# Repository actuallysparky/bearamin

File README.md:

# Bearamin

A whole copse of Bearamin friends. I made this family of optical instruments to turn a little motion into a lot of musical possibility.

Move your paw above an 8×8 depth sensor to shape X, Y and Z, find a note, open a gate, or give it a Spank. Pick the Bearamin that fits your patch:

| Bearamin | What it does | What you need |
| --- | --- | --- |
| [Bearamin Lite](bearamin-lite/README.md) | Gesture-controlled Eurorack CV and gates, plus USB and Bluetooth MIDI | Optical VL53L7CX sensor  paired with an ESP32-S3 Matrix |
| [Bearamin Virtual](bearamin-virtual/README.md) | Gesture control for VCV Rack and USB MIDI for your DAW | VL53L7CX sensor and an RP2040-Zero carrier |
| [Bearamin](bearamin/README.md) | A specialist nerd tool for droners: five sound and CV modes, presets, and a browser interface | Sensor head, MatrixCore, Wi-Fi sidecar, and a dsp.coffee DPT |

## Find your sound

The shared **[Bearamin Field Guide](https://actuallysparky.github.io/bearamin/)** hangs out in a cave by Salmon Lake and connects to Bearamin Lite and Bearamin Virtual, helping you map motion to MIDI, get the latest firmware for your device, and generally be cool af. USB MIDI works with Lite and Virtual; Bluetooth MIDI works with Lite. Use a browser that supports Web MIDI, such as Chrome or Edge.

## See Bearamin in action

**[Watch “Bearamin Jazz” (2:29)](bearamin/media/bearamin-jazz.mp4?raw=1)**

## Make a Bearamin

Want one but don't wanna singe your fur with a soldering iron? Stay tuned - built modules available soon from Hive Mind Synthesis. 

Each product folder contains its firmware source and current editable KiCad hardware designs. Virtual also includes its VCV Rack 2 plugin. The releases are **beta releases**; start with the instructions for your hardware and the matching firmware.

Build reports, patches, and musical experiments are welcome. [Open an issue](https://github.com/actuallysparky/bearamin/issues) and tell me what you’re making.

## A deep bow to Mutable Instruments

Bearamin’s resonator modes build on **Émilie Gillet’s extraordinary work at Mutable Instruments**. Rings and stmlib come from [pichenettes/eurorack](https://github.com/pichenettes/eurorack); their original copyright and MIT license notices are retained. Bearamin is an independent derivative project, with enormous gratitude for the generosity and imagination behind that work.

## Full credit to dsp.coffee

The full instrument is built on the **dsp.coffee DPT**, designed and openly shared by **Joe Misra**. It provides the Daisy-based audio engine, CV and gate I/O, and the expansion connection Bearamin uses. Explore the [DPT source](https://github.com/joemisra/dpt) and [dsp.coffee](https://dsp.coffee/).

## Other upstream work

This family also builds on the [Electro-Smith Daisy ecosystem](https://github.com/electro-smith/libDaisy), [Espressif Arduino core](https://github.com/espressif/arduino-esp32), [Raspberry Pi Pico SDK](https://github.com/raspberrypi/pico-sdk), [TinyUSB](https://github.com/hathach/tinyusb), [NimBLE-Arduino](https://github.com/h2zero/NimBLE-Arduino), [ArduinoJson](https://github.com/bblanchon/ArduinoJson), ST’s VL53L7CX sensor driver, and Adafruit’s [VL53L7CX](https://github.com/adafruit/Adafruit_VL53L7CX) and [NeoPixel](https://github.com/adafruit/Adafruit_NeoPixel) libraries. Virtual’s predecessor is [BearaminVirtual](https://github.com/actuallysparky/BearaminVirtual).

## License

The existing Bearamin source and hardware use the [MIT License](LICENSE). Third-party files retain their upstream licenses and notices. Virtual’s Rack plugin is licensed under GPL-3.0-or-later; its bundled Bearfield processor retains the MIT License.

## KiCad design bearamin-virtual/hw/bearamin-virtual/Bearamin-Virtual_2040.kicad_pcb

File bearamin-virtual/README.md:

# Bearamin Virtual

An optical gesture controller for VCV Rack and USB MIDI. The display lives in Rack; the hardware stays small.

A Waveshare RP2040-Zero connects to a VL53L7CX 8×8 depth sensor through the six-pin carrier. It presents USB serial and class-compliant USB MIDI at the same time, so Rack and your DAW can share the controller without a bridge process.

## Play

In VCV Rack 2, add **Bearamin Virtual**, then select its serial port in the module context menu. The module shows the depth field and provides X/Y/Z unipolar and bipolar CV, Presence and Spank outputs.

In your DAW, choose **Bearamin Virtual** as a MIDI input. Defaults: channel 1, CC 20/21/22 for X/Y/Z, CC 23 for Presence, and note 60 for Spank. Virtual uses USB; it has no Bluetooth or Wi-Fi.

Open the [Bearamin Field Guide](https://actuallysparky.github.io/bearamin/) to change MIDI and gesture settings or install the current firmware. After the initial UF2 installation, compatible application updates transfer through MIDI and preserve saved settings. The full UF2 includes the recovery loader; firmware before the new loader requires that initial installation.

## Sources

- `firmware/BearaminVirtual2040/`: Pico SDK firmware, sensor driver and recovery loader.
- `vcv/BearaminVirtual/`: Rack 2 plugin and panel assets.
- `hw/bearamin-virtual/`: current RP2040-Zero carrier, schematic and footprints.

These are beta releases. Sensor wiring is GP12 SDA, GP9 SCL, GP14 LPn and GP13 INT. The six-pin sensor header also carries 3.3 V and ground.

Firmware uses Pico SDK 2.1.1. Rack builds require the Rack 2 SDK and Jansson. MIDI updates verify SHA-256 integrity and accept a trusted USB host; they are not signed updates.

[Family, credits and licensing](../README.md)

## Build

Set `PICO_SDK_PATH` to Pico SDK 2.1.1 with its submodules, then run `./test.sh` and `./build.sh`. Build the Rack plugin with `make -C vcv/BearaminVirtual RACK_DIR=/path/to/Rack-SDK`, followed by its `dist` target.

## VCV Rack plugin

The Rack plugin is version **2.0.1**, licensed under **GPL-3.0-or-later**. The shared Bearfield processor retains its MIT license; both license notices are included in the plugin package.

Download the matching `.vcvplugin` package from the [Rack plugin release](https://github.com/actuallysparky/bearamin/releases/tag/rack-BearaminVirtual-2.0.1). Packages are available for Windows x64, Linux x64 (glibc 2.34+), Intel Mac x64 and Apple Silicon Mac ARM64. Close Rack, place the matching package in its user folder's `plugins-win-x64`, `plugins-lin-x64`, `plugins-mac-x64` or `plugins-mac-arm64` directory, and restart Rack. Requires the Bearamin Virtual RP2040-Zero and VL53L7CX sensor; the plugin reads its USB serial stream.

From the repository root, run `make RACK_DIR=/path/to/Rack-SDK dist` to build the Rack package. The root build forwards to `bearamin-virtual/vcv/BearaminVirtual/` and publishes its output in the root `dist/` directory. Linux and Windows native builds and wire/protocol/output tests passed. All four packages have verified architecture, manifest, license contents and checksums. Physical controller operation in Rack has been confirmed on macOS ARM64; Windows, Linux and Intel Mac still need live controller/Rack testing.

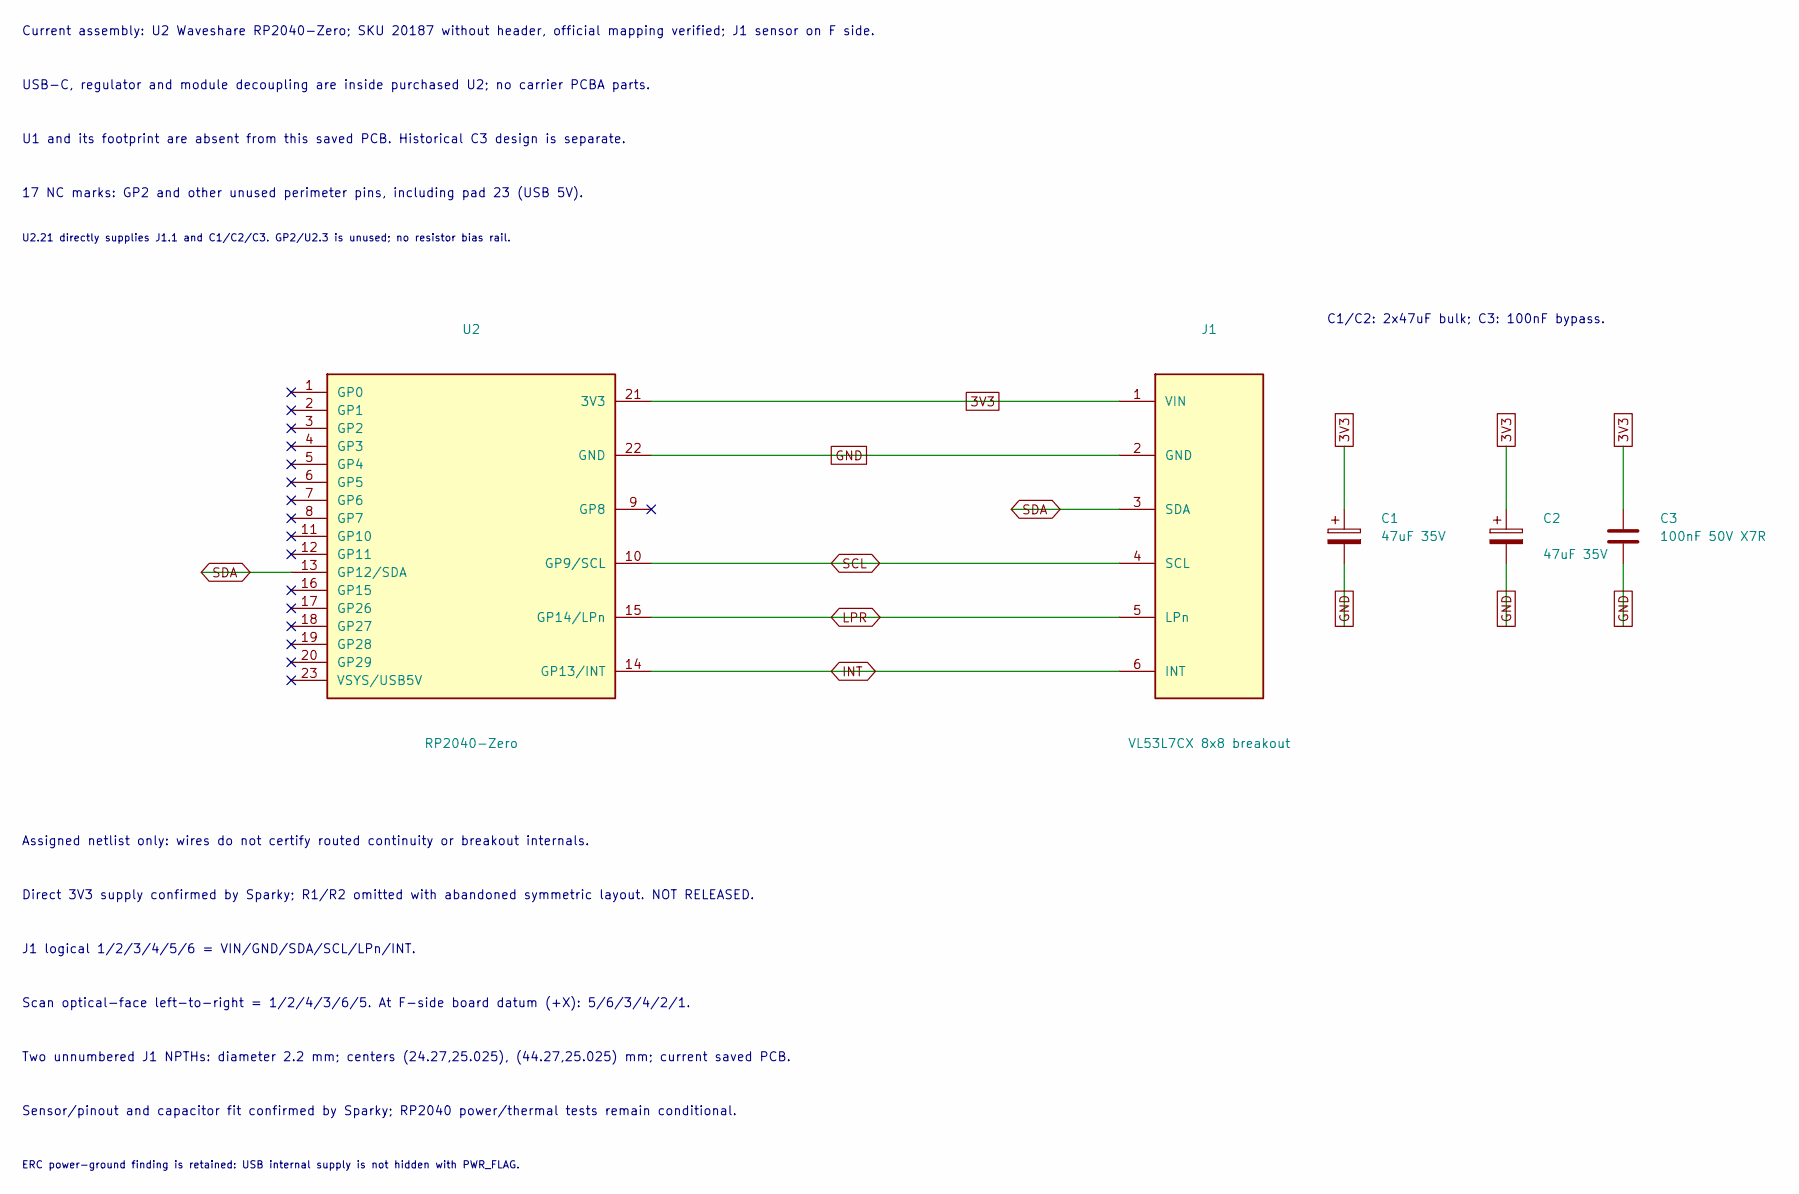
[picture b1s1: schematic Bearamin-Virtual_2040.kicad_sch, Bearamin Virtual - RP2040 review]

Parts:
C1, C2: 47uF 35V; CP_Radial_D5.0mm_P2.00mm; MPN 35ZLH47MEFC5X11
C3: 100nF 50V X7R; C_Disc_D5.0mm_W2.5mm_P5.00mm; MPN RDER71H104K0M1H03A
J1: VL53L7CX 8x8 breakout; VL53L7CX_8x8_J1_ScanMount
U2: RP2040-Zero; RP2040-Zero_1x23

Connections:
3V3: C1.1, C2.1, C3.1, J1.1 (VIN), U2.21 (3V3)
GND: C1.2, C2.2, C3.2, J1.2 (GND), U2.22 (GND)
INT: J1.6 (INT), U2.14 (GP13/INT)
LPR: J1.5 (LPn), U2.15 (GP14/LPn)
SCL: J1.4 (SCL), U2.10 (GP9/SCL)
SDA: J1.3 (SDA), U2.13 (GP12/SDA)

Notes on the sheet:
Current assembly: U2 Waveshare RP2040-Zero; SKU 20187 without header, official mapping verified; J1 sensor on F side.
USB-C, regulator and module decoupling are inside purchased U2; no carrier PCBA parts.
U1 and its footprint are absent from this saved PCB. Historical C3 design is separate.
17 NC marks: GP2 and other unused perimeter pins, including pad 23 (USB 5V).
Assigned netlist only: wires do not certify routed continuity or breakout internals.
Direct 3V3 supply confirmed by Sparky; R1/R2 omitted with abandoned symmetric layout. NOT RELEASED.
J1 logical 1/2/3/4/5/6 = VIN/GND/SDA/SCL/LPn/INT.
Scan optical-face left-to-right = 1/2/4/3/6/5. At F-side board datum (+X): 5/6/3/4/2/1.
Two unnumbered J1 NPTHs: diameter 2.2 mm; centers (24.27,25.025), (44.27,25.025) mm; current saved PCB.
Sensor/pinout and capacitor fit confirmed by Sparky; RP2040 power/thermal tests remain conditional.
ERC power-ground finding is retained: USB internal supply is not hidden with PWR_FLAG.
C1/C2: 2x47uF bulk; C3: 100nF bypass.
U2.21 directly supplies J1.1 and C1/C2/C3. GP2/U2.3 is unused; no resistor bias rail.

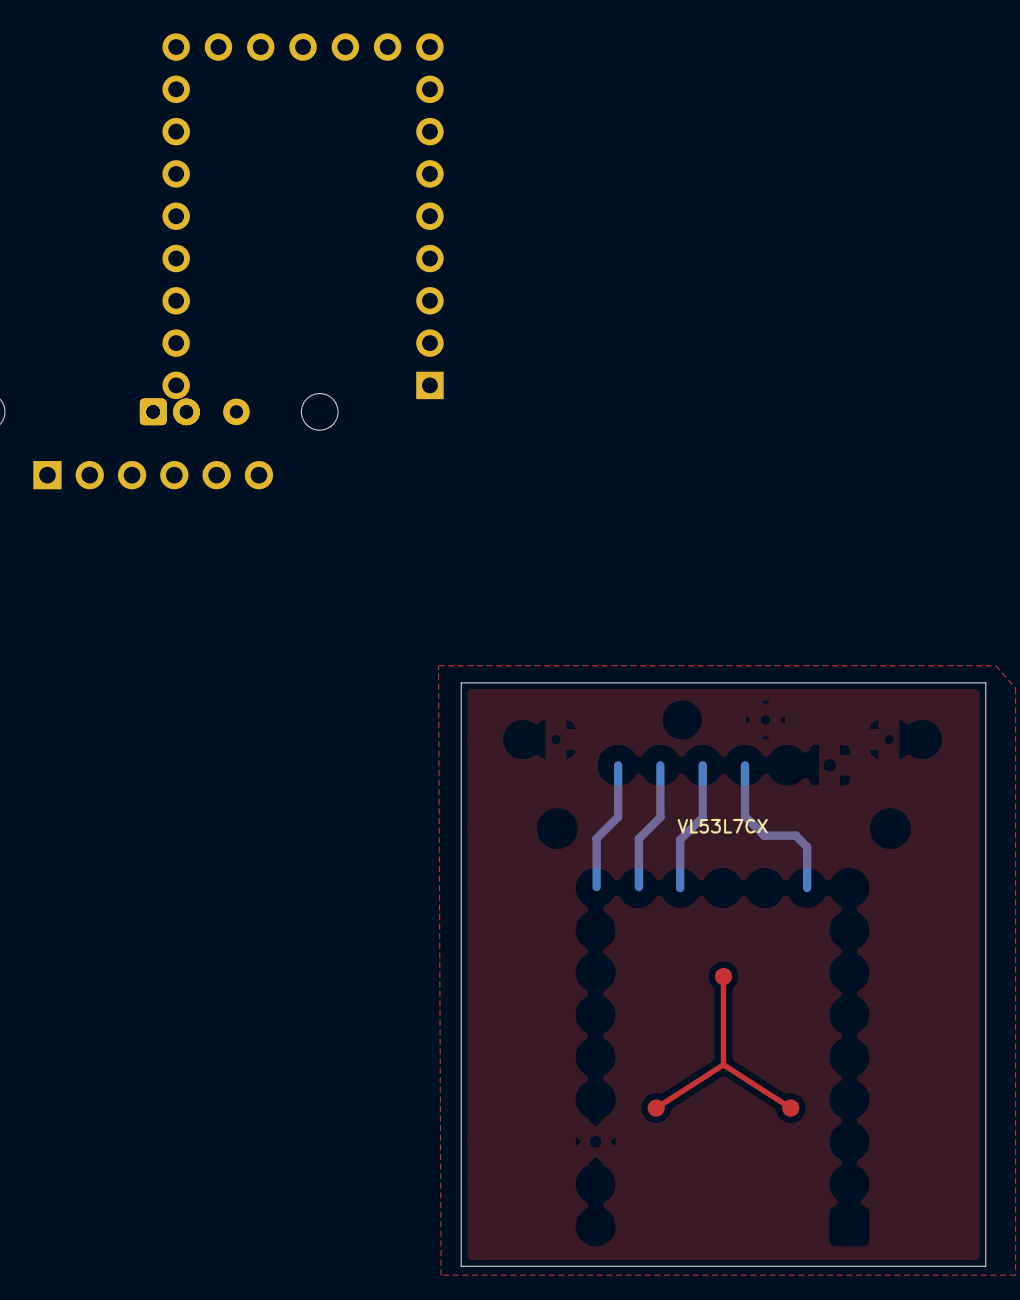
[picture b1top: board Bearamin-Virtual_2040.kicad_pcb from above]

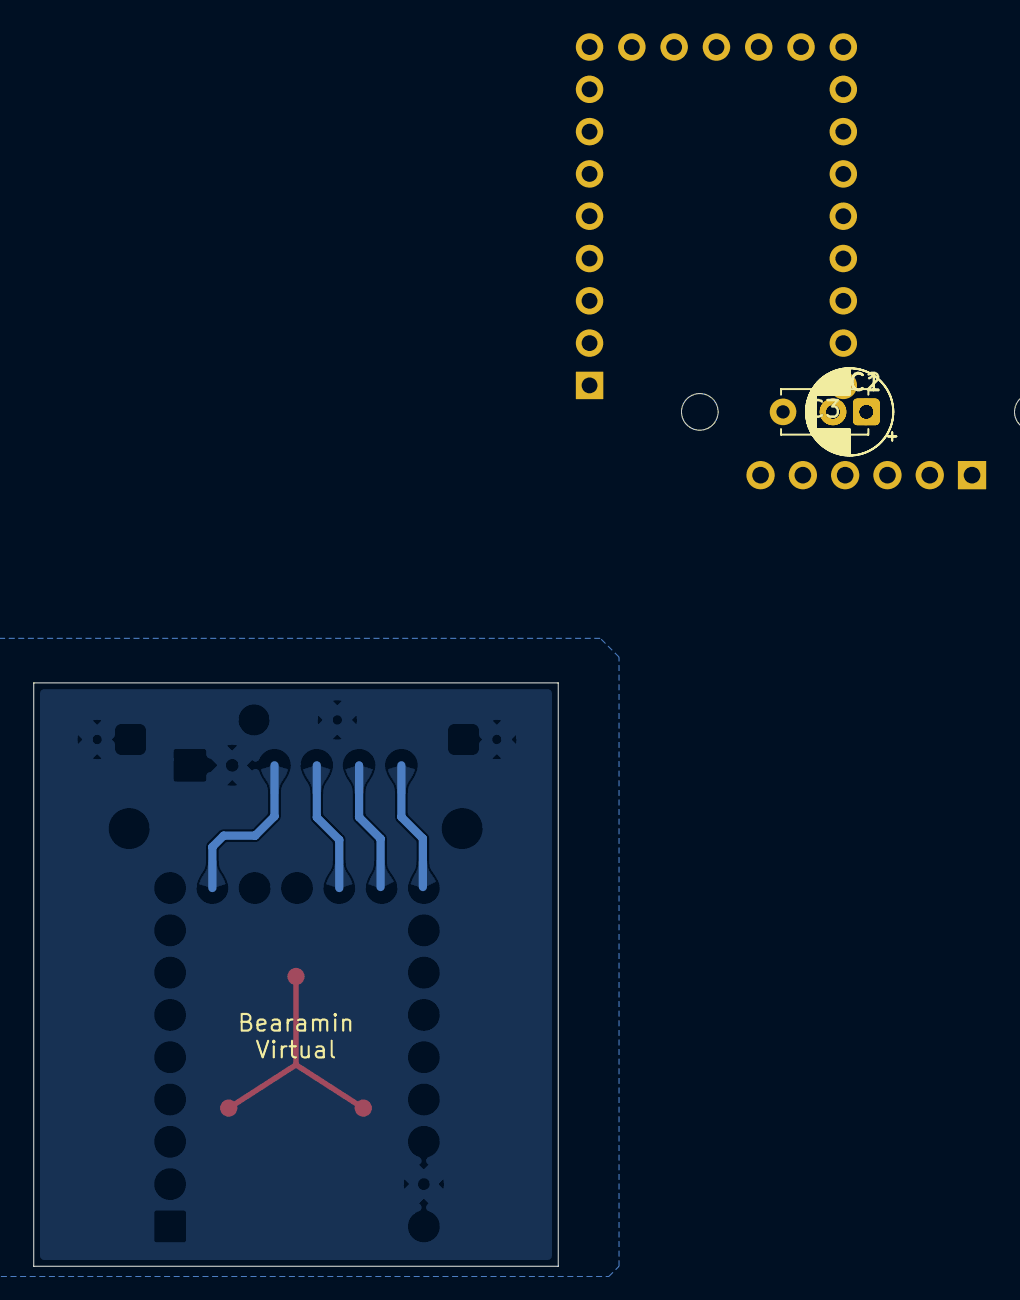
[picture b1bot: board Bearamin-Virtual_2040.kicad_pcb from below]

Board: 2 copper layers, 31.5 x 35.0 mm, 5 parts (4 on the bottom side), 6 nets.

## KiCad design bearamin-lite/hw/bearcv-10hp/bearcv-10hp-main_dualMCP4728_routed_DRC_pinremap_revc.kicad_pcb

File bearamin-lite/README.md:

# Bearamin Lite

A small optical controller for your Eurorack patch, with USB MIDI and Bluetooth MIDI for the rest of your studio.

Move above the VL53L7CX sensor to control X/Y/Z CV in unipolar and bipolar ranges, Presence and Spank gates. The ESP32-S3 Matrix supplies the depth display; Range and Slew keep the gesture response close at hand. Lite uses two MCP4728 DACs and has no DPT dependency.

## MIDI and settings

Connect USB, or connect Bluetooth MIDI in your computer's MIDI settings, then open the [Bearamin Field Guide](https://actuallysparky.github.io/bearamin/). The guide discovers your device and lets you change MIDI mapping, gesture response, orientation and LED brightness.

Defaults: channel 1, CC 20/21/22 for X/Y/Z, CC 23 for Presence, and note 60 for Spank. Bluetooth discovery opens for two minutes after startup; resetting pairings opens another two-minute window. Lite has no Wi-Fi interface.

## Sources

`firmware/BearaminLiteMidi/` contains the MIDI firmware; its production CV behavior shares `firmware/BearCV/`, `firmware/common/`, `firmware/targets/` and Bearfield processing. `hw/bearcv-10hp/` contains the current Bourns Rev C main board, schematic and matching faceplate.

These are beta releases. Rev C retains its recorded potentiometer-cutout clearance issue; review that geometry before ordering a board.

The MIDI build requires Arduino ESP32 3.3.12, ArduinoJson 7.4.3, NimBLE-Arduino 2.5.0, Adafruit VL53L7CX 1.0.0 and NeoPixel 1.15.5. First installation replaces internal settings and Bluetooth pairings.

[Family, credits and licensing](../README.md)

## Build

With Arduino CLI installed, run `./setup.sh`, `./test.sh`, then `./build.sh` from this folder. The setup installs the pinned dependencies; images and build metadata stay in `_local/latest-roms/bearamin-lite-midi/`.

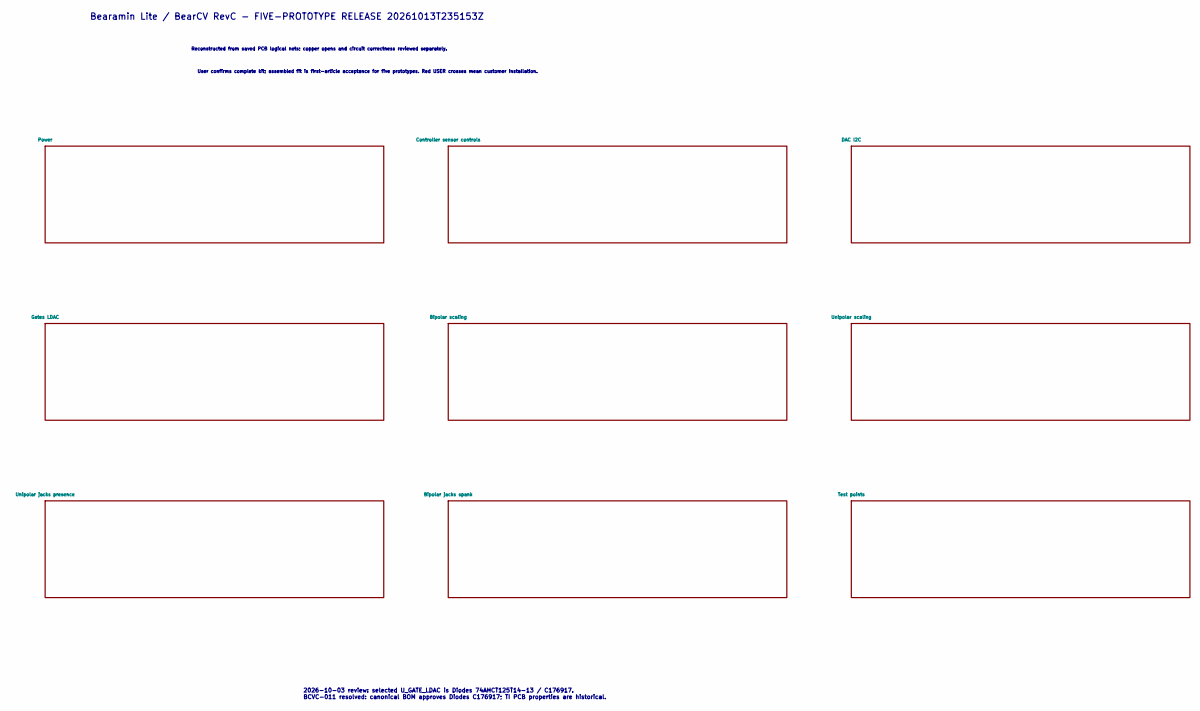
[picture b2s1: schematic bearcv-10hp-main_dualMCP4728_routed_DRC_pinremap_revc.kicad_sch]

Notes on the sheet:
Bearamin Lite / BearCV RevC - FIVE-PROTOTYPE RELEASE 20261013T235153Z
Reconstructed from saved PCB logical nets; copper opens and circuit correctness reviewed separately.
User confirms complete kit; assembled fit is first-article acceptance for five prototypes. Red USER crosses mean customer installation.
2026-10-03 review: selected U_GATE_LDAC is Diodes 74AHCT125T14-13 / C176917. BCVC-011 resolved: canonical BOM approves Diodes C176917; TI PCB properties are historical.

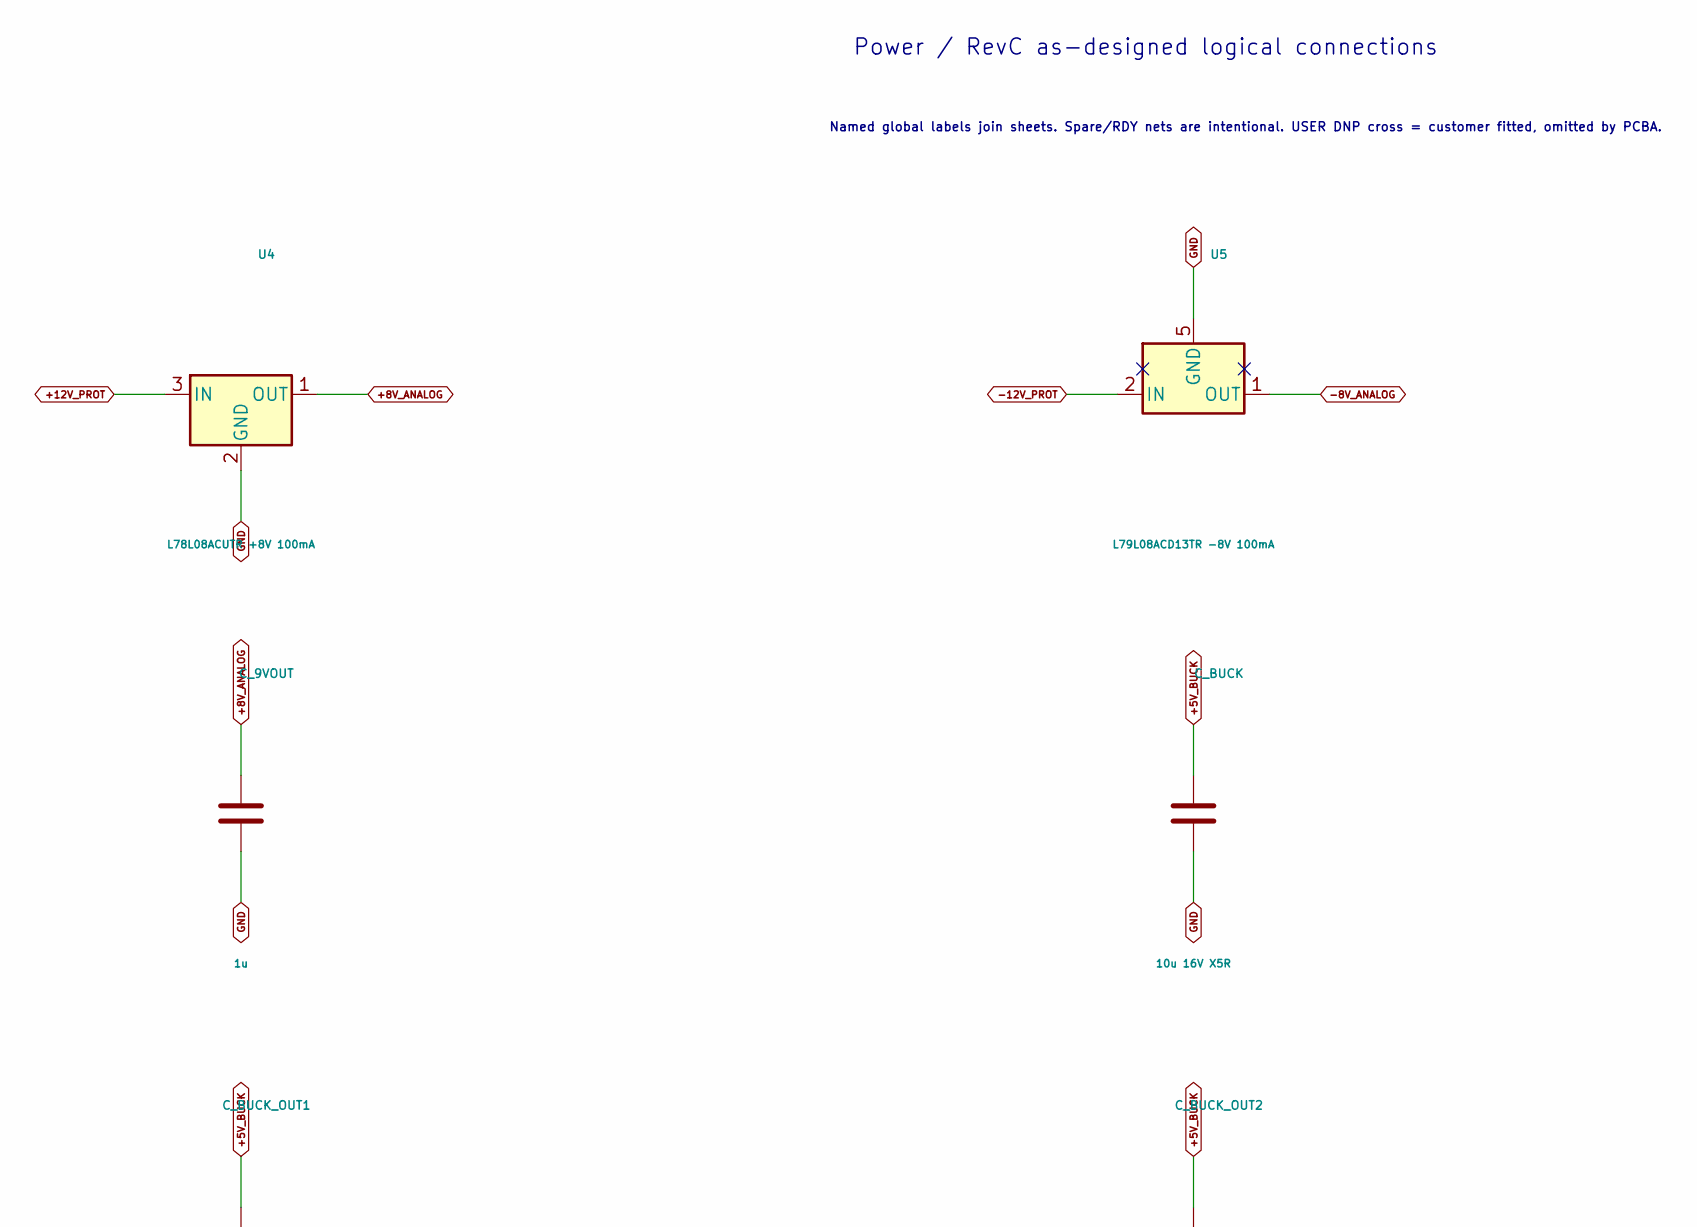
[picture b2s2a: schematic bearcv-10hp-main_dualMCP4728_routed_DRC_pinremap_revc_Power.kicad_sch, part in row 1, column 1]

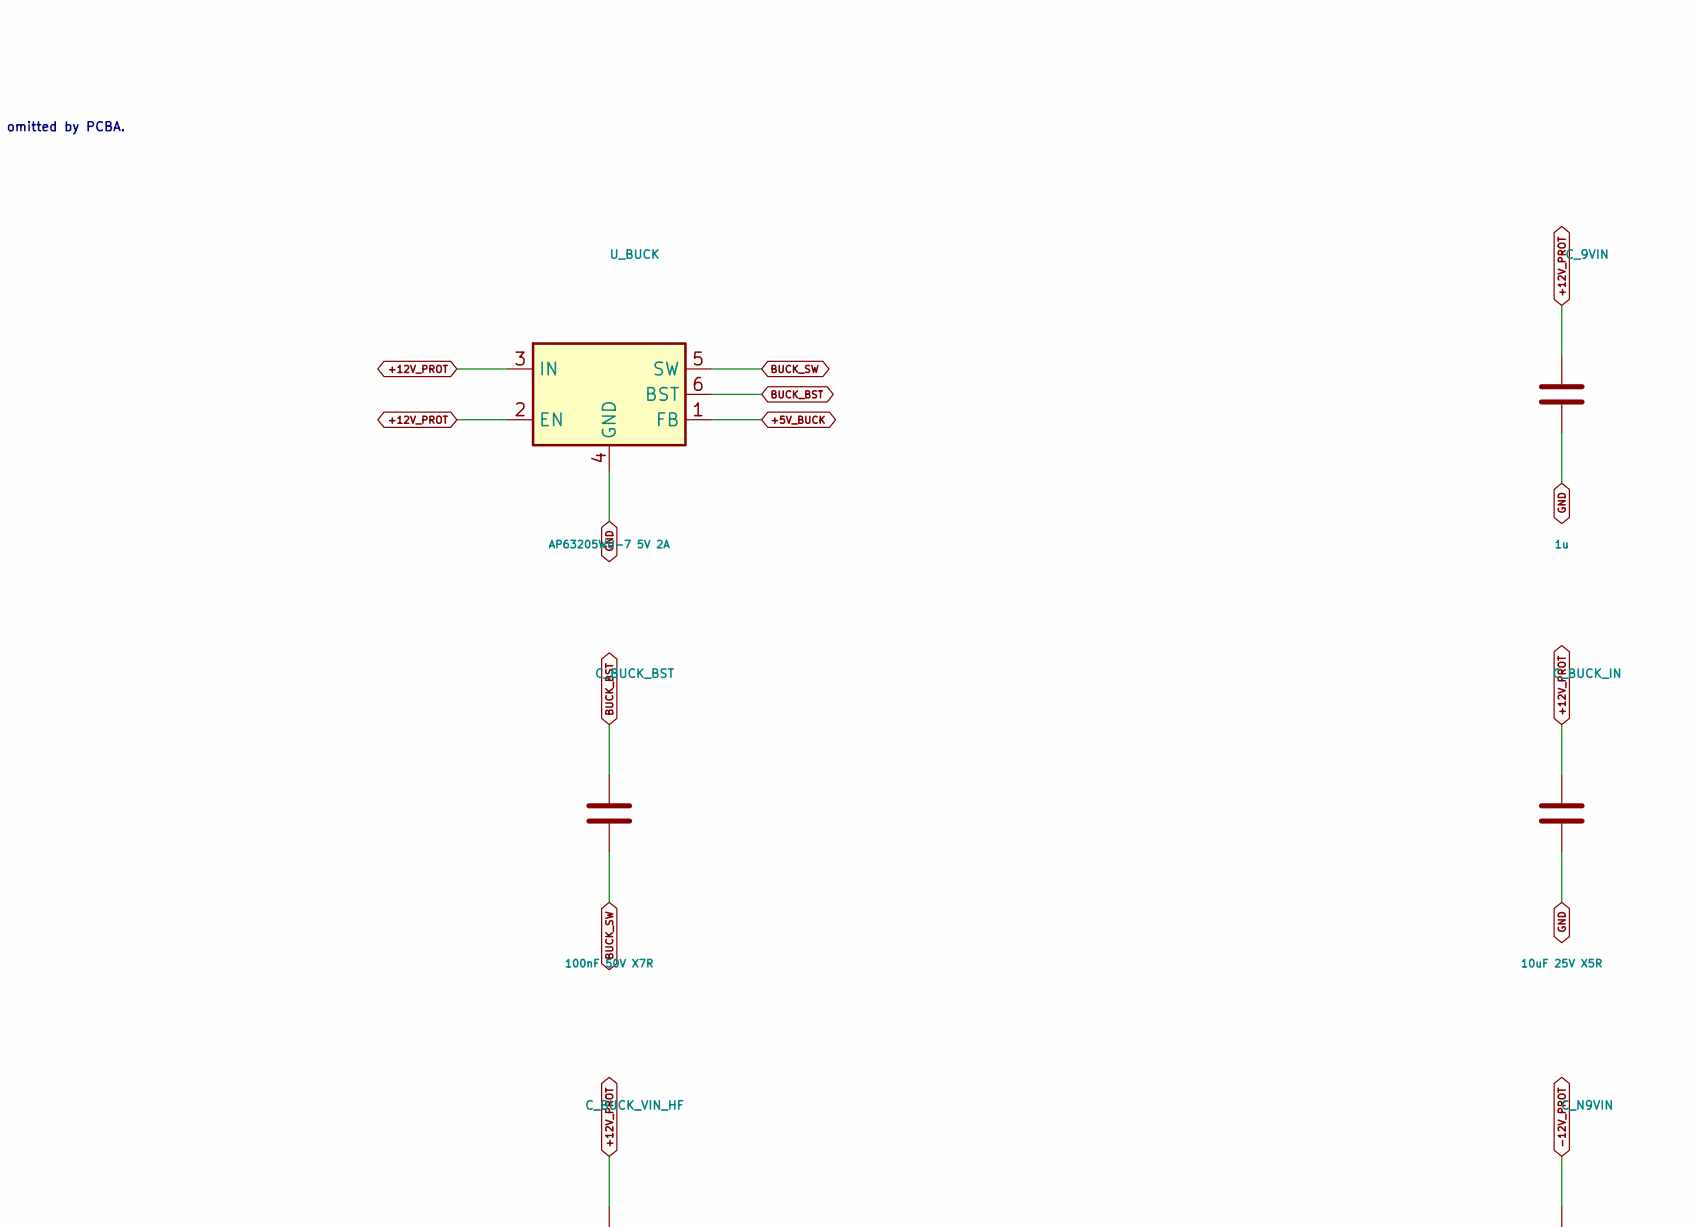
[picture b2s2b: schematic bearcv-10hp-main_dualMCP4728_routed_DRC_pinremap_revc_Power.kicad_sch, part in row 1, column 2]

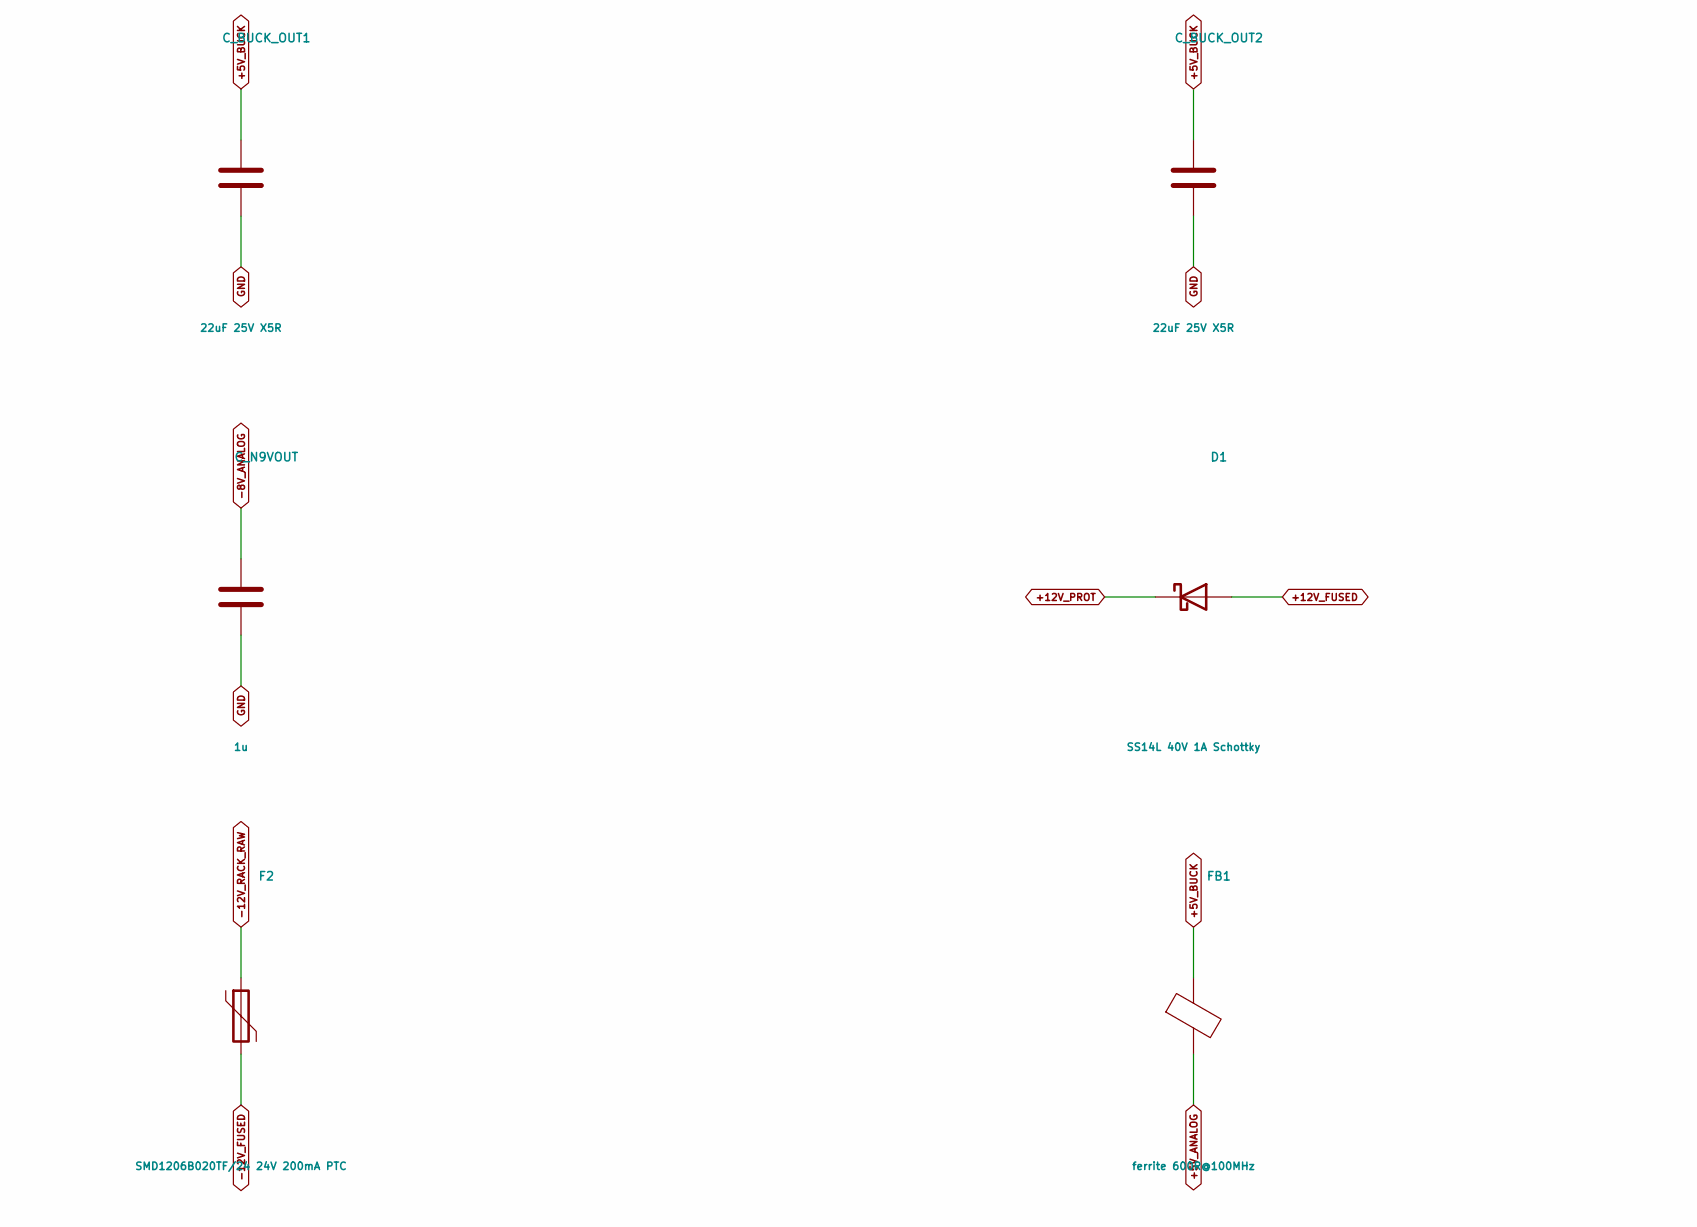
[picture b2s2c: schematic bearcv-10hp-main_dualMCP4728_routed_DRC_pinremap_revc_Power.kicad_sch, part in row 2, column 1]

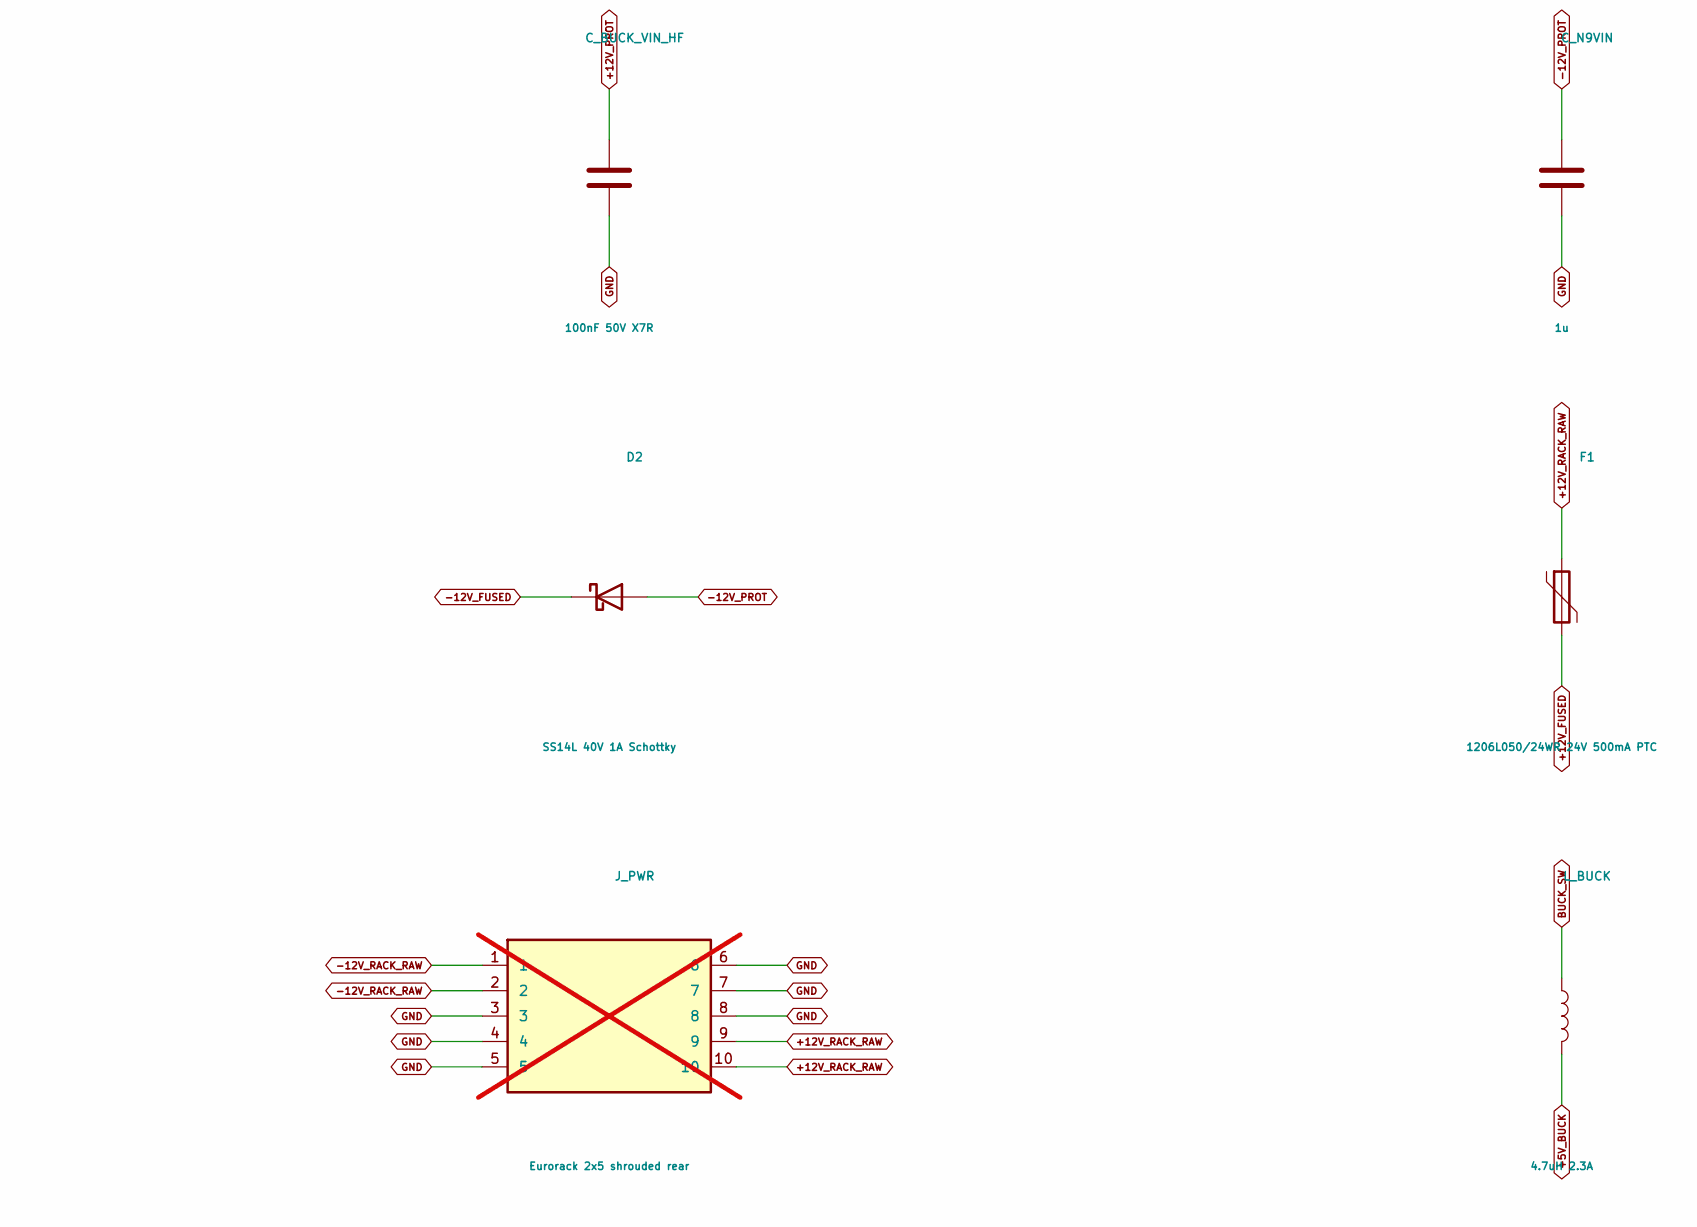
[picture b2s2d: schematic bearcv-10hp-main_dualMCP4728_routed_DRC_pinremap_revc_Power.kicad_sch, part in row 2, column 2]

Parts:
C_9VIN, C_9VOUT: 1u; MPN CL10A105KB8NNNC; JLCPCB Part C15849
C_BUCK: 10u 16V X5R; MPN CL10A106MA8NRNC; JLCPCB Part C96446
C_BUCK_BST: 100nF 50V X7R; MPN CC0603KRX7R9BB104; JLCPCB Part C14663
C_BUCK_IN: 10uF 25V X5R; MPN CL21A106KAYNNNE; JLCPCB Part C15850
C_BUCK_OUT1, C_BUCK_OUT2: 22uF 25V X5R; MPN CL21A226MAQNNNE; JLCPCB Part C45783
C_BUCK_VIN_HF: 100nF 50V X7R; MPN CC0603KRX7R9BB104; JLCPCB Part C14663
C_N9VIN, C_N9VOUT: 1u; MPN CL10A105KB8NNNC; JLCPCB Part C15849
D1, D2: SS14L 40V 1A Schottky; MPN SS14L; JLCPCB Library Extended
F1: 1206L050/24WR 24V 500mA PTC; MPN 1206L050/24WR; JLCPCB Library Extended
F2: SMD1206B020TF/24 24V 200mA PTC; MPN SMD1206B020TF/24; JLCPCB Library Extended
FB1: ferrite 600R@100MHz; MPN GZ1608D601TF; JLCPCB Part C1002
J_PWR: Eurorack 2x5 shrouded rear; IDC-Header_2x05_P2.54mm_Vertical; MPN DNP; not fitted
L_BUCK: 4.7uH 2.3A; MPN SLW4020P4R7MST; JLCPCB Part C207886
U4: L78L08ACUTR +8V 100mA; MPN L78L08ACUTR; JLCPCB Library Extended
U5: L79L08ACD13TR -8V 100mA; MPN L79L08ACD13TR; JLCPCB Library Extended
U_BUCK: AP63205WU-7 5V 2A; MPN AP63205WU-7; JLCPCB Part C2071056

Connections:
+5V_ANALOG: FB1.2; also elsewhere on the board
+5V_BUCK: C_BUCK.1, C_BUCK_OUT1.1, C_BUCK_OUT2.1, FB1.1, L_BUCK.2, U_BUCK.1 (FB); also elsewhere on the board
+8V_ANALOG: C_9VOUT.1, U4.1 (OUT); also elsewhere on the board
+12V_FUSED: D1.2 (A), F1.2
+12V_PROT: C_9VIN.1, C_BUCK_IN.1, C_BUCK_VIN_HF.1, D1.1 (K), U4.3 (IN), U_BUCK.2 (EN), U_BUCK.3 (IN); also elsewhere on the board
+12V_RACK_RAW: F1.1, J_PWR.9, J_PWR.10
-8V_ANALOG: C_N9VOUT.1, U5.1 (OUT); also elsewhere on the board
-12V_FUSED: D2.1 (K), F2.2
-12V_PROT: C_N9VIN.1, D2.2 (A), U5.2 (IN), U5.3 (IN), U5.6 (IN), U5.7 (IN); also elsewhere on the board
-12V_RACK_RAW: F2.1, J_PWR.1, J_PWR.2
BUCK_BST: C_BUCK_BST.1, U_BUCK.6 (BST)
BUCK_SW: C_BUCK_BST.2, L_BUCK.1, U_BUCK.5 (SW)
GND: C_9VIN.2, C_9VOUT.2, C_BUCK.2, C_BUCK_IN.2, C_BUCK_OUT1.2, C_BUCK_OUT2.2, C_BUCK_VIN_HF.2, C_N9VIN.2, C_N9VOUT.2, J_PWR.3, J_PWR.4, J_PWR.5, J_PWR.6, J_PWR.7, J_PWR.8, U4.2 (GND), U5.5 (GND), U_BUCK.4 (GND); also elsewhere on the board

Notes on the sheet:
Power / RevC as-designed logical connections
Named global labels join sheets. Spare/RDY nets are intentional. USER DNP cross = customer fitted, omitted by PCBA.
